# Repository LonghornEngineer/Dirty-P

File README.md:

# Dirty-P
Guitar FX pedal driven by 3 2N3906 transistors

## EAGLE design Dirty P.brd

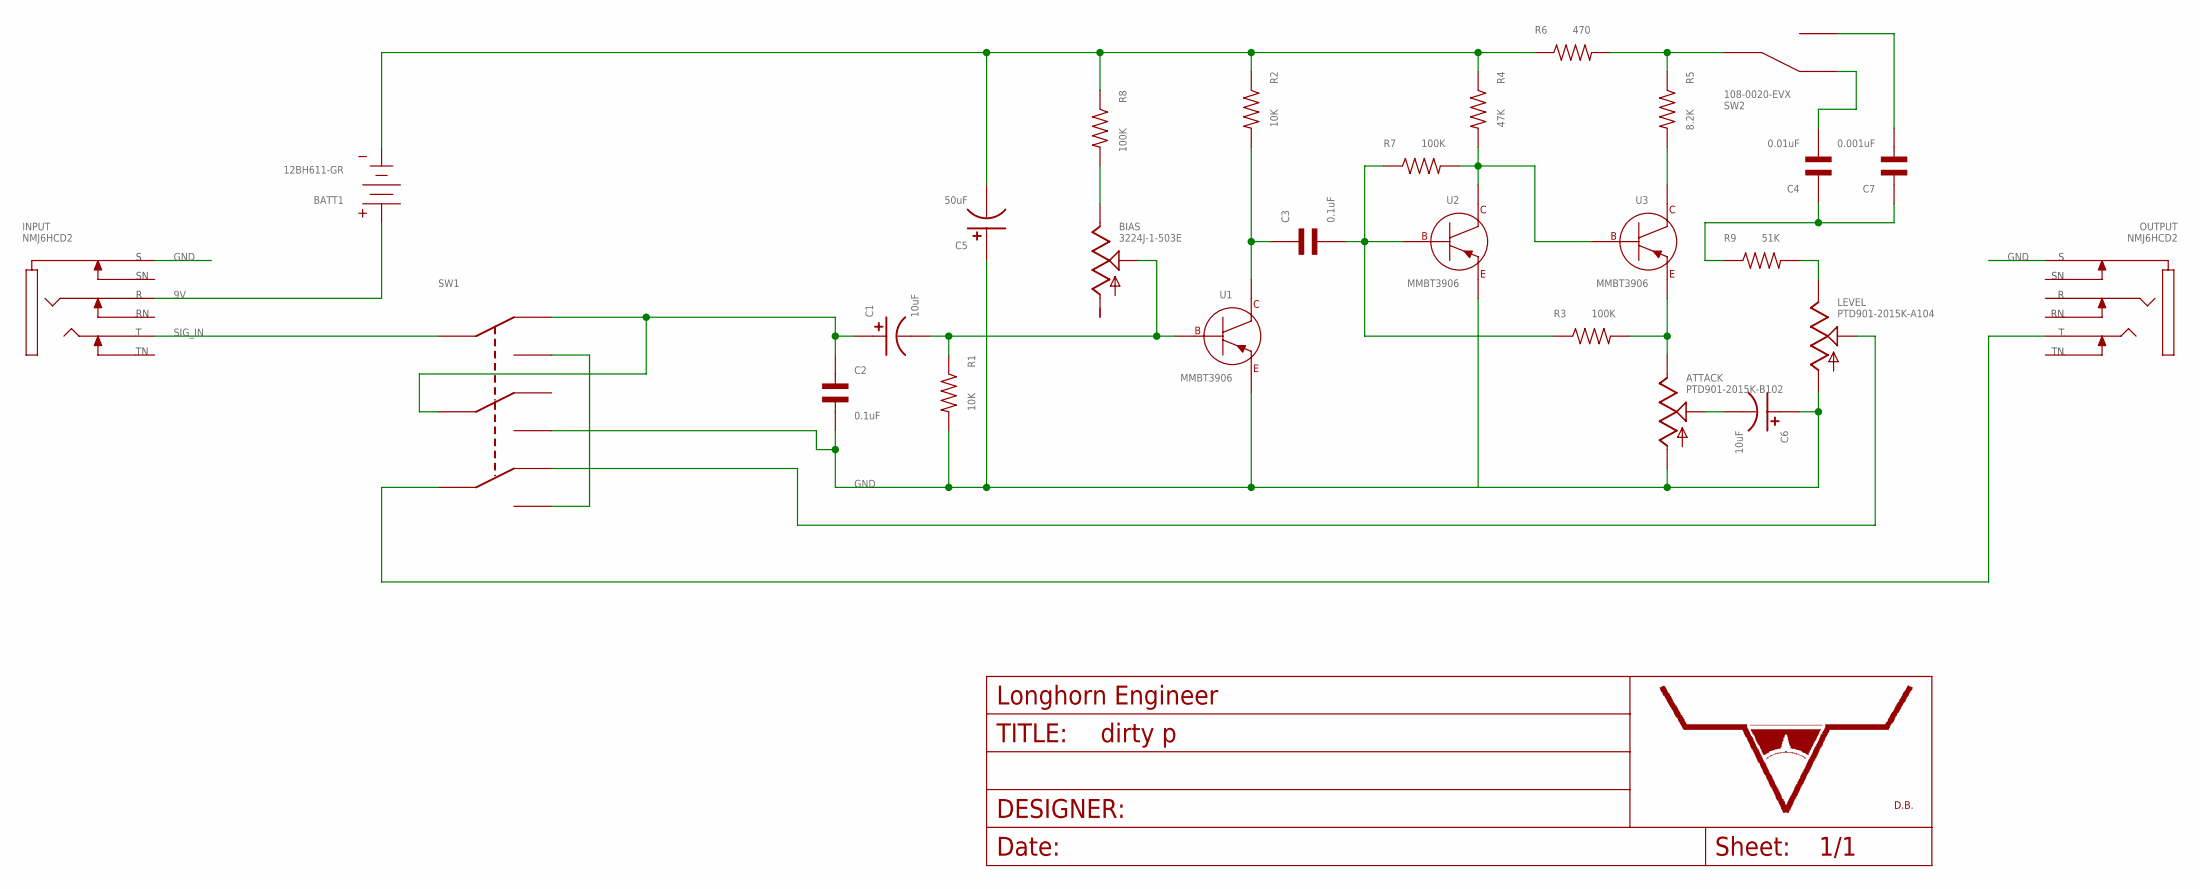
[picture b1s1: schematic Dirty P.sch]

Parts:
ATTACK: PTD901-2015K-B102; PTD901
BATT1: 12BH611-GR
BIAS: 3224J-1-503E; 3224J
C1, C6: 10uF; CP4MM
C2, C3: 0.1uF; C0805
C4: 0.01uF; C0805
C5: 50uF; CP8MM
C7: 0.001uF; C0805
INPUT: NMJ6HCD2
LEVEL: PTD901-2015K-A104; PTD901
OUTPUT: NMJ6HCD2
R1, R2: 10K; R0805
R3, R7, R8: 100K; R0805
R4: 47K; R0805
R5: 8.2K; R0805
R6: 470; R0805
R9: 51K; R0805
SW1: 3PDT_STOMPBOX_SW; STOMPBOX_SW
SW2: 108-0020-EVX
U1, U2, U3: MMBT3906; SOT-23-3
U$1: LHE_FRAME
U$2: DB_LOGO_COPPER_MEDIUM; DB_COPPER_MEDIUM

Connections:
9V: BATT1.+, INPUT.R
GND: ATTACK.P$3 (3), C2.P$2, C5.P$1, C6.P$1, INPUT.S, LEVEL.P$3 (3), OUTPUT.S, R1.P$2, SW1.B3 (6), SW1.B6 (6), U1.P$2 (EMITTER), U2.P$2 (EMITTER)
unnamed: BIAS.2, C1.P$2, R1.P$1, U1.P$1 (BASE)
unnamed: C3.P$2, R3.P$1, R7.P$1, U2.P$1 (BASE)
unnamed: C3.P$1, R2.P$2, U1.P$3 (COLLECTOR)
unnamed: BATT1.-, C5.P$2, R2.P$1, R4.P$1, R6.P$1, R8.P$1
unnamed: R5.P$1, R6.P$2, SW2.P$2 (C)
unnamed: R4.P$2, R7.P$2, U2.P$3 (COLLECTOR), U3.P$1 (BASE)
unnamed: R5.P$2, U3.P$3 (COLLECTOR)
unnamed: ATTACK.P$1 (1), R3.P$2, U3.P$2 (EMITTER)
unnamed: ATTACK.P$2 (2), C6.P$2
unnamed: LEVEL.P$1 (1), R9.P$2
unnamed: OUTPUT.T, SW1.C2 (8), SW1.C5 (8)
unnamed: BIAS.3 (1), R8.P$2
unnamed: C4.P$1, C7.P$1, R9.P$1
unnamed: C1.P$1, C2.P$1, SW1.A1 (1), SW1.A4 (1), SW1.B2 (5), SW1.B5 (5)
unnamed: C4.P$2, SW2.P$1 (1)
unnamed: C7.P$2, SW2.P$3 (2)
unnamed: SW1.A3 (3), SW1.A6 (3), SW1.C3 (9), SW1.C6 (9)
unnamed: LEVEL.P$2 (2), SW1.C1 (7), SW1.C4 (7)
SIG_IN: INPUT.T, SW1.A2 (2), SW1.A5 (2)

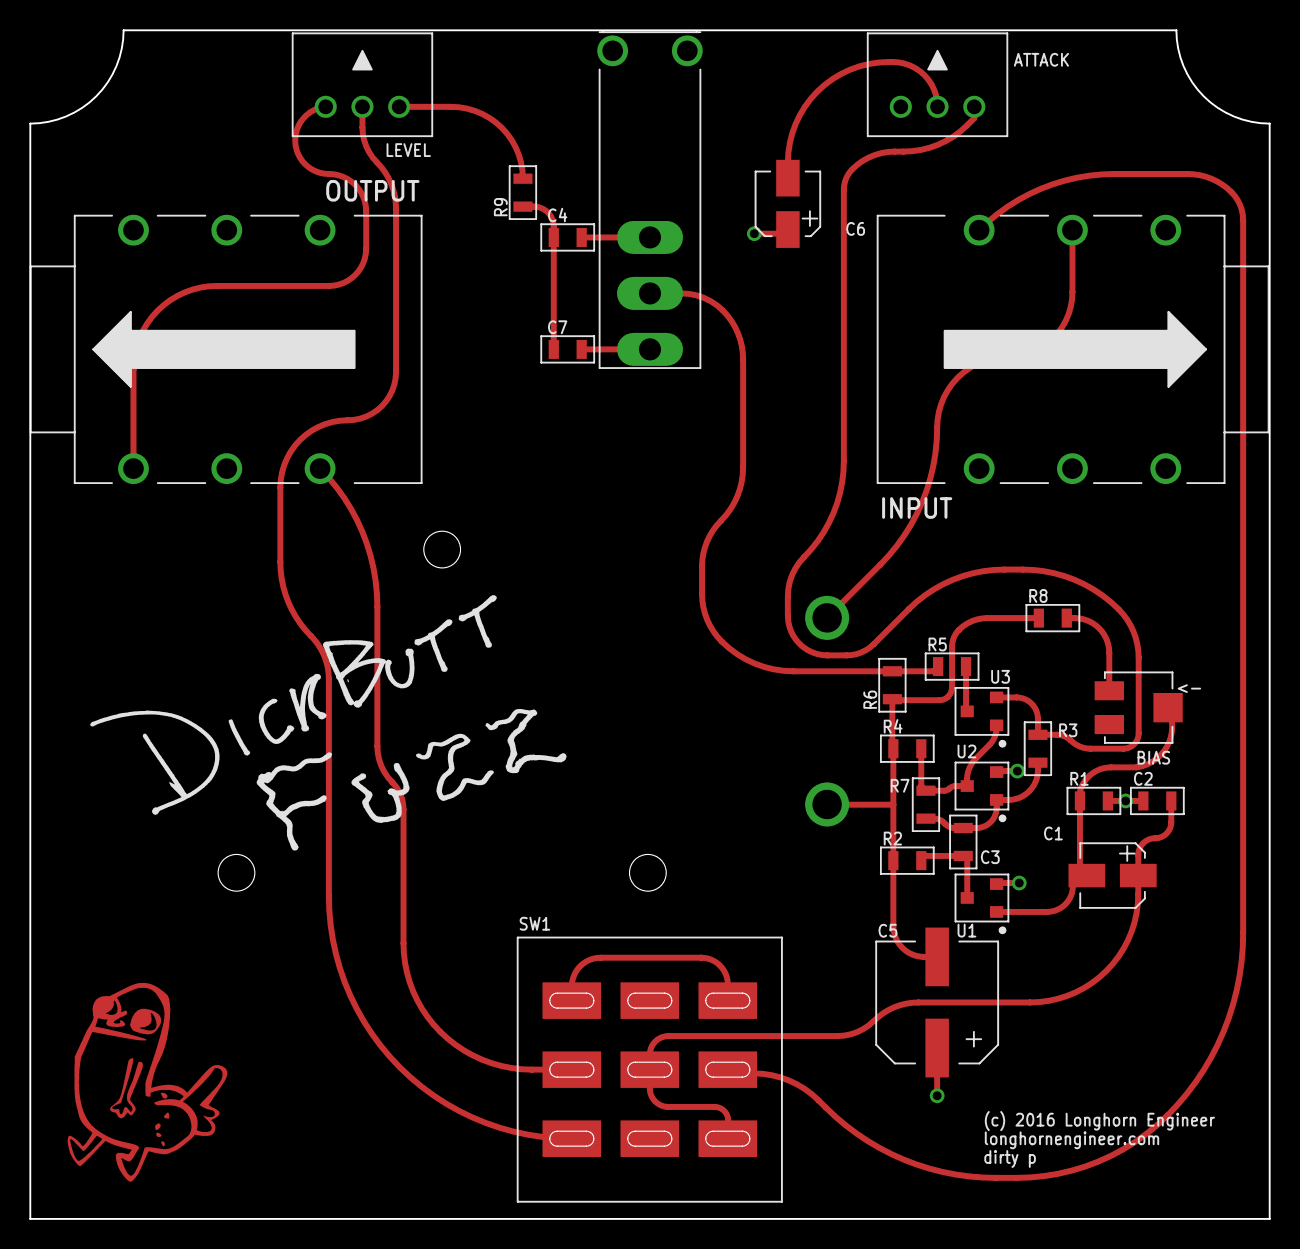
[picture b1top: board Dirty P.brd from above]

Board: 2 copper layers, 84.4 x 80.9 mm, 29 parts (1 on the bottom side), 21 nets.

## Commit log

2015-11-18 first push of files.
2015-11-18 switched to 4MM caps for 10uF
2015-12-22 REV2: Bass switch. Bias Pot added. Fixed connectors. Added space for Bosses.
2015-12-22 changed out switch and rerouted some stuff.
2015-12-22 Changed caps back
2015-12-23 changed R9 to 51K cause 50K doesnt really exist
2016-06-22 Rev 3 Complete.
2016-06-22 Adding Camfiles

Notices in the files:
parts and their libraries:
PP_Aesthetics: (c) 2016 Longhorn Engineer
